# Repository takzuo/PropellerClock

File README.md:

# PropellerClock
Library Arduino Propeller Clock

BY JULIAN DAVID ARANGO OREJUELA

Libreria para el diseño de un propeller clock con arduino 5 bits diseño y esquemas en http://www.lascomandas.com/propellerclock/ 

Se utiliza el puerto D del arduino nano

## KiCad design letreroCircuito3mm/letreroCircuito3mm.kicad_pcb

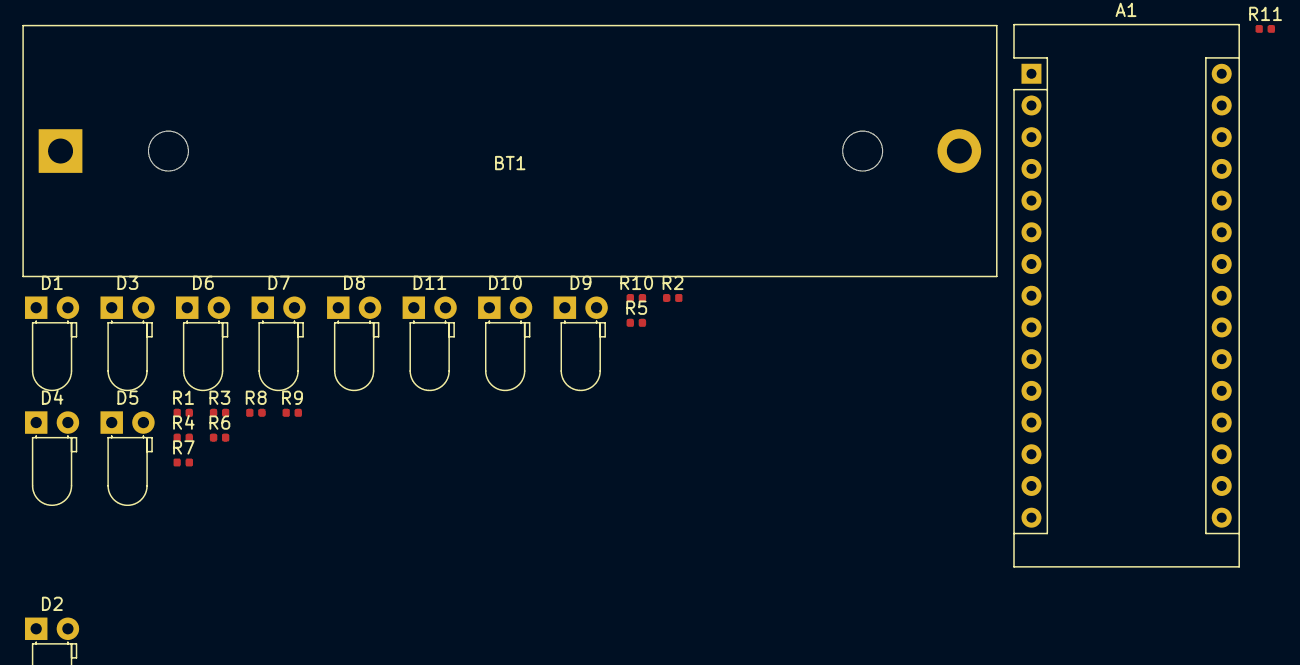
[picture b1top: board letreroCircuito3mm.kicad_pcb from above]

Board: 2 copper layers, 24 parts (0 on the bottom side), 23 nets, no tracks yet.

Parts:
A1: Arduino_Nano_v3.x; Arduino_Nano
BT1: 18650; BatteryHolder_MPD_BH-18650-PC2
D1, D2, D3, D4, D5, D6, D7, D8, D9, D10: LED; LED_D3.0mm_Horizontal_O1.27mm_Z2.0mm
D11: D_Photo; LED_D3.0mm_Horizontal_O1.27mm_Z2.0mm
R1, R2, R3, R4, R5, R6, R7, R8, R9, R10: 470; R_0402_1005Metric
R11: 10k; R_0402_1005Metric

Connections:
GND: A1.4, BT1.2, D1.1, D2.1, D3.1, D4.1, D5.1, D6.1, D7.1, D8.1, D9.1, D10.1, D11.2
unnamed: A1.5, D11.1, R11.2
unnamed: A1.6, R1.1
unnamed: A1.7, R2.1
unnamed: A1.8, R3.1
unnamed: A1.9, R4.1
unnamed: A1.10, R5.1
unnamed: A1.11, R6.1
unnamed: A1.12, R7.1
unnamed: A1.13, R8.1
unnamed: A1.14, R9.1
unnamed: A1.15, R10.1
unnamed: A1.27, BT1.1, R11.1
unnamed: D1.2, R1.2
unnamed: D2.2, R2.2
unnamed: D3.2, R3.2
unnamed: D4.2, R4.2
unnamed: D5.2, R5.2
unnamed: D6.2, R6.2
unnamed: D7.2, R7.2
unnamed: D8.2, R8.2
unnamed: D9.2, R9.2
unnamed: D10.2, R10.2
